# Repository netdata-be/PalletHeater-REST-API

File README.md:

# OpenPelletBridge – REST API for Micronova pellet stoves

> **Nederlandstalige handleiding voor gebruikers: [docs/handleiding.md](docs/handleiding.md).** The technical documentation is listed under [Documentation](#documentation).

> Formerly **PalletHeater**. Renamed after v1.0.0: the default hostname is now `openpelletbridge.local` (a hostname set under *IP settings* is kept), the default MQTT prefix `openpelletbridge` and the release asset `openpelletbridge-firmware.bin` (since v1.1.7 releases no longer carry `palletheater-firmware.bin`: a controller on v1.0.0 needs one manual upload). JSON fields such as `lowPalletAlarm` and the metric `stove_low_pallet_alarm` keep their names for compatibility.

ESP32 firmware that connects to the serial bus of a Micronova based pellet stove and exposes it over:

- a **web app** on `/` to monitor and control the stove from any browser,
- an **HTTP REST API** ([docs/api.md](docs/api.md)),
- a **BLE GATT service** (see [BLE_API.md](BLE_API.md)), used by the iOS app in [app/](app/) (OpenPelletBridge board only: the DevKit firmware is built without Bluetooth, it no longer fits the DevKit's app slot),
- **Prometheus metrics** on `/metrics`,
- a **telnet** debug menu on port 23 (IPv4 and IPv6): status, control, timers, pellets, errors, network, firmware update, live log.

The full OpenAPI 3 specification is in [docs/openapi.json](docs/openapi.json). The same file is embedded in the firmware and rendered with Swagger UI on `http://<device>/api`.

## Documentation

| Document | Contents |
|---|---|
| [docs/handleiding.md](docs/handleiding.md) | Handleiding voor gebruikers (Nederlands) |
| [docs/api.md](docs/api.md) | REST API: conventions, authentication, every endpoint, stove states and error codes |
| [docs/mqtt.md](docs/mqtt.md) | MQTT and Home Assistant, metrics, Bluetooth, telnet |
| [docs/loxone.md](docs/loxone.md) | Loxone: HTTP input with a line of numbers, pushes to the Miniserver (`/jdev/sps/io`), states and error ids |
| [docs/debugging.md](docs/debugging.md) | Serial link, live debugging, restart reason, core dump, firmware updates |
| [docs/development.md](docs/development.md) | Building and uploading, partitions, CI and releases, unit tests, source layout |
| [docs/discovered-values.md](docs/discovered-values.md) | What is known about the stove registers |
| [hardware/README.md](hardware/README.md) | Controller board (draft): schematic, BOM, design choices |
| [docs/openapi.json](docs/openapi.json) | OpenAPI 3 specification |

## Hardware

An ESP32 dev board (`esp32doit-devkit-v1`) on a custom PCB:

N-channel MOSFETs convert the 3.3 V TTL of the ESP32 to the 5 V TTL the stove expects. Micronova uses a single-wire serial bus where TX and RX are coupled, so everything the ESP32 transmits is also received; the firmware strips its own echo from the received bytes. The Fritzing design is in [Fritzing/](Fritzing/).

## Getting started

1. Flash the firmware (see [Development](docs/development.md#development)).
2. On first boot the device starts a WiFi captive portal. Connect to it and enter your WiFi credentials and NTP server.
3. Once connected, the device is reachable on its IP address or on `http://openpelletbridge.local` (mDNS).
4. Open `http://openpelletbridge.local/` for the web app, `http://openpelletbridge.local/device` for the fallback page or `http://openpelletbridge.local/api` for Swagger UI.

Hold the reset button for 5 seconds to wipe the WiFi settings and restart the captive portal.

## Web app

`http://openpelletbridge.local/` (also `/app`) is a single page web app built into the firmware ([web/app.html](web/app.html)). It has no external dependencies, so it also works without internet access, and adapts to phone and desktop screens and to light/dark mode (automatic, or fixed with the theme button).

### A tour of the app

*The screenshots use sample data; names and addresses are examples.*

**Overview.** The top card shows the state of the stove in words (here: standby because energy saving stopped it, and the temperature at which it starts again), the next timer action, the room temperature, set point and fume temperature, and the power button. Below it: set point, flame power and room fan; energy saving with its stop and restart temperatures; and the status values the stove reports. The *Update* button in the header appears when a newer firmware release is available.

**History.** One chart with a lane per quantity on a shared time axis: temperatures, flame power (set and actual), room fan and, on request, fume temperature, auger and fume fan speed. The dotted lines mark every change of the stove state (from the event log), labelled where there is room. Hover or tap for the values at that moment. Choose 30 min up to 24 h (a point every 2 minutes)…

…or *7 d*: hourly averages of the last week, with *Burning*, the share of each hour the stove was heating.

**Remote control, settings and clock.** A read-only copy of what the remote control shows (here *OFF / ENERGY / OK*: standby by energy saving after the stove has cooled down, with the chrono clock icon and the "E" for energy saving), the combustion and pellet quality corrections and the beep, and the stove clock next to NTP and the browser time with buttons to set it.

**Timers.** The six chrono programs of the stove: on and off time, days, set point, flame power and room fan per program, with *Copy to…* to reuse a program. Above them: what the next timer will do.

**Device, network and MQTT** (*Expert* on). Stove and controller firmware, what the firmware is built for, why the controller last (re)started and how often it crashed, Bluetooth and API key, the firmware update from GitHub (*Install vX*), settings backup and restore. *Network (WiFi)* shows the connection and how often it dropped and why; *Other network* and *IP settings* change it. *MQTT* shows the broker connection and opens its settings. *Loxone* sets up the push to a Loxone Miniserver: per value the virtual input that receives it (searched in the Miniserver's own list), the switch that follows on / off, and a test.

**Console** (button *Console* in the header, shown in Debug mode and whenever the stove does not answer; or Ctrl+`). A panel docked at the bottom like the browser's developer tools, with a draggable edge; it stays usable when the stove is unreachable. Three tabs: *Firmware log*, *Stove bus* and *Requests* (the API calls of the page itself with status and duration). *Firmware log* shows what the controller writes to its serial port, with the time; warnings are orange, errors red. After a restart it starts with the last lines from before it. *Log levels per module* sets how much each part writes.

*Stove bus* shows every read and write between the controller and the stove as one line: time, action, register (RAM or EEPROM and address), value (decimal and hex) and what the value means according to the known register table, with the previous value when it changed (*← was 140*). *Changes only* (on by default) shows the first reading of each register and after that only changes, writes and failures. The legend under the output explains the colours. *Raw bytes* adds the bytes of each transaction on the serial line, in hex or (*Binary*) in bits, with what each part is: TX is what the controller sends (read: type, address; write: 0x80 + type, address, value, checksum), RX what it receives: the echo of TX (the bus is one wire), then the stove's answer (checksum, value), with the checksum checked. A timeout shows how many bytes did arrive. Filter on addresses (`0x21, 0x6E`) or text; *Download* saves the lines.

**Dark mode.** The theme button in the header (◐ automatic, ☀ light, ☾ dark) switches between following your phone or computer and a fixed light or dark theme; the choice is kept per browser and included in a settings backup.

### Features

- **Status:** stove state, room / set point / fume temperatures, the sensor the room temperature comes from (derived from the readings), the wireless sensor setting, sensors, fume fan, auger speed, pellet level, error memory, stove vs NTP clock, firmware, starts and working hours. Refreshes every 5 s from `/api/state`.
- **Alerts:** a banner for alarms (states 8 – 10), an active error code, no answer from the stove, low pellets, stale data and an unreachable controller.
- **Settings backup:** *Back up settings* under *Device* downloads a JSON file with the stove settings, timers, MQTT (without password), network, device options and display choices; *Restore settings* writes the parts you tick back through the normal API (no passwords or API key in the file).
- **Status dots:** two dots in the header: *Stove* for the serial link between the controller and the stove (green OK, red the stove does not answer, orange data older than 30 s) and the controller dot for the connection between the page and the controller (green with the time of the last update, red offline). On a phone only the stove dot is shown.
- **Update badge:** when a newer release is available an *Update* button appears in the header, next to the version.
- **Home screen:** the app has a web app manifest and icon (`/manifest.webmanifest`, `/icon.svg`, `/icon-180.png`), so *Add to Home Screen* (iOS Safari, Android Chrome) gives it its own icon and a full-screen window. (Installing as a real PWA, and browser push notifications, need HTTPS with a certificate the device trusts: open `https://openpelletbridge.local/` after installing the controller's self-signed certificate on it, see [`/api/https`](docs/api.md#apihttps); the home screen shortcut works over HTTP too.)
- **History:** one chart for the last 30 min / 1 / 6 / 12 / 24 h or 7 days (hourly averages, with the share of each hour the stove was burning) (from `/api/history`) with toggles for room, set point, stove sensor, remote sensor, flame power, room fan, fume temperature, auger speed, fume fan speed and vertical lines at the exact stove state changes (from `/api/events`), plus a list of the state changes with their duration. Each quantity has its own lane and scale on a shared time axis, with one crosshair tooltip and a table view.
- **Remote control:** a read-only mirror of the remote display (time and date, room temperature, flame power blocks 1 – 4, room fan, "E" for energy saving, OFF screen, error, open menu) plus menu, selected parameter, language and last contact.
- **Controls:** power on/off, set point, flame power, room fan, energy saving, combustion and pellet quality, beep, clock sync, delete single errors or the whole error memory, restart.
- **Timers:** edit, enable/disable and copy PR1 – PR6 (to one program or all others), plus the next scheduled timer action. A program that could not be read from the stove is shown as *Read error* and cannot be saved, so a bad read is never written back.
- **Help:** (i) buttons next to settings, clock, timers and error codes with explanations taken from the stove manual (FWAR01).
- **Clock:** sync the stove clock to NTP or to the browser time.
- **Expert / Debug:** two toggles in the header (remembered per browser). *Expert* shows technical details: wireless sensor setting, fume fan, auger, brazier cleaning countdown, controller firmware / build / uptime, firmware upload, API / metrics links and the history table. *Debug* shows research and diagnostics: raw registers (room fan power RAM 0x0A, pellet reserve sensor / counter, raw remote edit value), serial errors and retries, the telnet switch and the EEPROM presets per power level (auger, fume fan). What is not verified yet is in [docs/discovered-values.md](docs/discovered-values.md).
- **Network and MQTT:** a *Network (WiFi)* card (network, signal, IP address, gateway, hostname; DHCP or static IP and hostname can be changed), an *MQTT* card (connection status, broker, topic prefix, discovery; settings) and a *Loxone* card (Miniserver push, see [Loxone](docs/loxone.md)). A small page with links is on `/device`.
- **Unreachable:** when the controller does not answer every card is greyed out and disabled; when only the stove does not answer (state −1) every card except *Device* is.
- **Language:** Dutch when the remote control language is NLD, otherwise English; `/app?lang=nl` / `/app?lang=en` overrides it.

To change the app, edit `web/app.html` and rebuild; it is embedded gzipped via `board_build.embed_files` like the OpenAPI spec.

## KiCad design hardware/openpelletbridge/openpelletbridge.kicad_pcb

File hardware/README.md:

# Controller board (draft 0.1)

[← README](../README.md)

A small board for the controller: ESP32-S3 module, USB-C, power from the stove or from USB, an isolated interface to the Micronova serial line, status LEDs, a buzzer, two buttons, test pads and four M2 mounting holes. **Draft: schematic and a first routed PCB.** Have it reviewed before ordering.

| File | |
|---|---|
| [openpelletbridge/openpelletbridge.pdf](openpelletbridge/openpelletbridge.pdf) | Schematic (PDF) |
| [openpelletbridge/openpelletbridge.kicad_sch](openpelletbridge/openpelletbridge.kicad_sch) | KiCad 10 schematic (open the `.kicad_pro`) |
| [openpelletbridge/bom.csv](openpelletbridge/bom.csv) | Bill of materials |
| [TODO.md](TODO.md) | **What has to happen when the board is made and taken into use** (checks, firmware port) |
| [openpelletbridge/openpelletbridge.net](openpelletbridge/openpelletbridge.net) | Netlist |
| [openpelletbridge/openpelletbridge.kicad_pcb](openpelletbridge/openpelletbridge.kicad_pcb) | PCB, 40 × 57 mm, 2 layers |
| [tools/gen_schematic.py](tools/gen_schematic.py) | Generates the schematic: the netlist is defined there |
| [tools/gen_pcb.py](tools/gen_pcb.py) | Generates the PCB: placement, outline, rules, isolation, planes |
| [tools/build.sh](tools/build.sh) | Schematic → ERC → netlist → PCB → [Freerouting](https://github.com/freerouting/freerouting) → planes → DRC |

The schematic is generated: change [tools/gen_schematic.py](tools/gen_schematic.py), then

```bash
python3 hardware/tools/gen_schematic.py
cd hardware/openpelletbridge
kicad-cli sch erc --severity-all openpelletbridge.kicad_sch        # 0 violations
kicad-cli sch export pdf openpelletbridge.kicad_sch
```

The whole chain, PCB included (KiCad 10 and Java; Freerouting is the open-source autorouter):

```bash
FREEROUTING=/path/to/freerouting-2.5.0.jar hardware/tools/build.sh
```

Freerouting is chaotic: a small change can leave a few connections open, so the script tries three strategies (all nets at once, signals first, ground planes first) until DRC finds no unconnected item. Once the board is finished by hand in KiCad, the KiCad files become the source and the scripts are no longer used.

## PCB

40 × 57 mm, 2 layers, all parts on the top (THT: J1 shell, J2); the bottom has only test pads and text, so nothing is assembled there. Antenna at the top edge (no copper below it on either layer), USB-C and the stove connector side by side on the bottom edge. Ground planes on both layers with stitching vias: GND for the controller, GND_S on the stove side (bottom left). A copper-free strip separates the two sides under the optocouplers; only JP1 / JP2 cross it. Four M2 holes (not plated, no copper within 2.4 mm, so a metal screw or standoff connects nothing): two at the sides of the buzzer band, two in the bottom corners. The top corners are in the antenna keep-out of the module (Espressif: no metal within 15 mm of the antenna).

Rules: tracks 0.2 mm (power 0.4 mm), clearance 0.2 mm, vias 0.6 / 0.3 mm, 0.3 mm from the board edge: within the standard capabilities of the usual PCB makers. DRC: no errors, no unconnected items; the remaining warnings are silkscreen (module outline over the top edge, labels close to parts).

Silkscreen: descriptions instead of references (USB-C, OPTO TX / OPTO RX, BUZZER, 5V BUCK, 3V3 LDO; the references are in the assembly drawing), GND / 5V / 20V / DATA at the stove connector, RESET and BOOT at the buttons, SYS · STOVE under the status LEDs, TX and RX at the serial LEDs (each just above its optocoupler, so they read as part of the stove link), STOVE PWR with + (JP1, 20 V) and − (JP2, ground) at the solder jumpers. On the bottom: the names of the test pads, "Micronova serial port board" (in the copper-free antenna strip), the name and version, and the input range "Power: 12-24 V DC (stove) or USB-C 5 V".

Not yet done: a final manual review of the routing (the autorouter's tracks are functional, not pretty). Production files: see *Ordering* below; open checks: [TODO.md](TODO.md).

3D models the KiCad library lacks are in [openpelletbridge/3d](openpelletbridge/3d): the ESP32-S3-MINI-1 from Espressif's [kicad-libraries](https://github.com/espressif/kicad-libraries), the WS2812B-2020 (C965555), the TS-1187A buttons (C318884) and the Kefa header (C441173, footprint in [openpelletbridge/openpelletbridge.pretty](openpelletbridge/openpelletbridge.pretty)) from LCSC / EasyEDA (fetched with easyeda2kicad).

## Case

3D printable case, [case/openpelletbridge-case.scad](case/openpelletbridge-case.scad) ([OpenSCAD](https://openscad.org), parametric), ready to print: [base](case/openpelletbridge-case-base.stl) and [lid](case/openpelletbridge-case-lid.stl). Outside 45 × 62 × 16.4 mm (plus two mounting ears with a 4.2 mm hole; `ears = false` without).

- **No screws:** the board (1.6 mm) drops onto four standoffs whose 1.9 mm pegs go into its M2 holes, and the lid's four clamping tubes press it onto the standoffs. The lid clicks in with four snap hooks (two per long side) that catch in windows in the walls; to open, push the hooks in through the windows with a small screwdriver. (The board's holes are M2, 2.2 mm, not plated, no copper within 2.4 mm, if you ever want screws instead.)
- **Buttons:** BOOT and RESET are flexure tongues in the lid with a plunger 0.3 mm above the tactile switch.
- **LEDs:** solid light pipes (2.2 mm) from the translucent lid down to just above SYS, STOVE, TX and RX; a slot in the lid's underside between SYS and STOVE keeps their colours apart. `solid_pipes = false` gives hollow tubes with a hole through the lid instead (for an opaque lid).
- **Connectors:** opening for the USB-C cable's overmould (13 × 7.5 mm); the stove connector's notch is open through the lid, so a cable plug of any height fits.
- **Other:** sound holes above the buzzer, engraved button labels (BOOT, RST; no other text: small engraved text gives thin-wall errors in resin). Plastic only near the antenna (top edge).
- **Material:** ordered in resin at JLCPCB (JLC3DP): base in **9600 Resin White** (sanding), lid in **8001 Resin Translucent** (fine sanding). Resin is brittle: the hook arms are 0.9 mm with a fillet at the root (~1.3 % strain when they click in), and no wall is under JLC3DP's 0.8 mm minimum. Ask for the supports on the inside of the lid, so the top stays smooth. Open the lid gently, and use a washer on the mounting ears.
- **FDM instead:** base upright, lid upside down (top face on the bed), 0.2 mm layers, no supports; PETG rather than PLA for the hooks.
- **Checked** against the board's 3D model (KiCad STL export): no part of the case inside a component, and the lid's hooks sit in the windows, not in the walls. Regenerate after a board change: `kicad-cli pcb export stl --subst-models --user-origin 100x157mm -o case/board.stl openpelletbridge/openpelletbridge.kicad_pcb`, then `openscad -D 'part="base"' -o … case/openpelletbridge-case.scad` (`"lid"`, or `"assembly"` with the board).

## Design

| Block | Choice | Why |
|---|---|---|
| Module | ESP32-S3-MINI-1-N8 (15.4 × 20.5 mm) | 8 MB flash (the firmware uses 91 % of a 4 MB layout), dual core, BLE 5, native USB: no USB-serial chip or auto-reset circuit |
| USB | USB-C GCT USB4105-GF-A, 5.1 kΩ on CC1 / CC2, USBLC6-2SC6, 0.5 A PTC | Power and flashing / console from a PC; D+ / D- straight to IO20 / IO19 |
| Stove power | 20 V → AP63205 step-down → 5 V, 0.35 A / 30 V PTC, 24 V TVS | A 7805 from 20 V burns ~3 W at the WiFi peaks. Input range **12 – 24 V**: above 24 V the TVS starts to conduct; worst case (WiFi peak, buzzer, LEDs full white) the board takes ~2.9 W, 0.24 A at 12 V, below the 350 mA hold current of F2. The buck itself needs ~7 V for 5 V out. F2 mainly protects the stove: a short on this board, or the TVS clamping, trips it instead of loading the stove's supply |
| Stove 5 V | Only for the LED of the RX optocoupler U6 (a few mA) | The controller never runs from the stove's 5 V |
| Power mux | TPS2116 in priority mode: stove (VIN1) first, USB (VIN2) as fallback; then AP2112K-3.3 | Both sources at once: with the stove's 5 V present the board runs from the stove and USB only carries data. USB takes over when the stove's 5 V drops below ~4.3 V (33k / 10k on PR1; VREF 1.0 V ± 8 % gives 4.0 – 4.6 V). Break-before-make in ~8 µs (22 µF on +5V: ~0.2 V dip at 0.5 A), reverse current blocked both ways. ST → IO4: high = powered by the stove. Replaces two LM66100 ideal diodes, which had CE on GND and so did not block reverse current (TI: only with CE on VOUT) and had no priority between two ~5 V sources |
| Isolation | JP1 + JP2 (solder jumpers) | Open: USB powered, stove side galvanically isolated. Closed: powered by the stove; GND_S is then tied to GND (and to the PC on USB) |
| Serial line | 2× LTV-357T (SO-4) | Level shift 3.3 V ↔ 5 V and isolation; the stove side runs on the stove's 5 V |
| Echo | Kept | The firmware tells "bus not connected" (no echo) from "stove does not answer" (echo, no answer) |
| TX / RX LED | Two 0603 LEDs on the serial lines themselves (no GPIO), above the optocouplers | Red = TX, green = RX: both while sending (echo), green when the stove answers, red only = no bus. They stay on the ESP side of the isolation (3V3, STOVE_TX / STOVE_RX) |
| Reverse polarity | B5819W Schottky in series with the stove's 20 V (after F2) | The stove's pin order is not standard: a swapped cable gives no current instead of a dead step-down. ~0.3 V drop at 0.1 A, no matter for the step-down |
| Buzzer | MLT-5020 magnetic transducer 5 × 5 mm on 3.3 V, AO3400A on IO21, 1N4148W flyback diode, 10 kΩ pull-down, 10 µF buffer | Needs a PWM signal (~4 kHz, LEDC); ~110 mA while it sounds. Silent during boot (pull-down). Operating temperature −30 – 70 °C: mind the place inside the stove |
| Test pads | 9 pads (1.5 mm) on the bottom: 3V3, 5V, GND, TX, RX under the module; 20V, 5V_S, DATA, GND_S on the stove side | Measuring at bring-up without probing the parts |
| Status LEDs | 2× WS2812B-2020 on IO8 via SN74LV1T34 (R8 10 kΩ pull-down on its input) | LED1 system (WiFi / Bluetooth / telnet / power), LED2 stove state; any colour and blink pattern, one GPIO |
| Buttons | RESET (EN, 10 kΩ / 1 µF) and BOOT / USER (IO0) | IO0 held during reset = download mode; otherwise a user button: 1× click / mute an alarm, 2× LEDs on / off, 3× buzzer on / off, hold 3 s = full reset countdown (8 s = reset, release = abort), see src/boardButton.h |
| Stove connector | Cixi Kefa KF2EDGR-3.5-4P header (LCSC C441173, 3.5 mm, right angle, THT); cable plug **KF2EDGKD-3.5-4P** (LCSC C441073, spring terminals, wires up to 1.5 mm²) | Same series from one maker, both at LCSC, so the plug surely fits; push the wires in, no crimping. Footprint and 3D model from LCSC / EasyEDA (holes 1.4 mm: the Phoenix footprint has 1.2 mm) |

### Serial interface

```
TX:  +3V3 ─ R5 220 ─ LED(U5) ─ STOVE_TX (IO17)          U5 transistor: DATA_S ─ GND_S
RX:  +5V_S ─ LED(U6) ─ R6 1.5k ─ DATA_S                  U6 transistor: STOVE_RX (IO18, 10k pull-up) ─ GND
```

STOVE_TX low switches U5 on and pulls the stove's data line low. Whenever DATA is low (the stove or our own TX), U6 pulls STOVE_RX low. R12 keeps STOVE_TX high while the ESP boots, so nothing reaches the bus before the UART runs. At 1200 baud (833 µs per bit) the optocouplers are fast enough.

Currents (Vf: optocoupler LED ~1.2 V, D5 / D6 ~2 V):

| Path | Current |
|---|---|
| IO17 low: U5 LED (R5 220) + D5 (R10 1.5k) + R12 | 9.5 + 0.9 + 0.3 = **10.7 mA** sunk by IO17 |
| DATA low: U6 LED from the stove's 5 V (R6 1.5k) | **2.5 mA**: the extra load on the stove's bus |
| U5 transistor, our TX | must sink the stove's pull-up + 2.5 mA; at CTR ≥ 100 % it can sink ≥ 9.5 mA, so the stove's pull-up may be down to ~750 Ω |
| U6 transistor, RX | R7 0.33 mA + D6 0.8 mA = 1.1 mA of the ≥ 2.5 mA it can sink |

D5 / D6 cannot change the logic levels: each sits between 3V3 (through 1.5k) and a line that is either high (3.3 V: no current) or pulled low by IO17 / U6, which then sink 0.8 – 0.9 mA more. While the ESP boots, STOVE_TX is high-impedance and R12 holds it high: D5 and U5 stay off, nothing reaches the bus. The stove's DATA pull-up is not known: measure it before connecting (see [TODO.md](TODO.md)).

### GPIO

| GPIO | Use |
|---|---|
| IO17 | STOVE_TX (UART1 TX) |
| IO18 | STOVE_RX (UART1 RX) |
| IO8 | WS2812B data |
| IO0 | BOOT / user button |
| IO21 | Buzzer (PWM, via Q1) |
| IO4 | Power source (TPS2116 ST): high = stove, low = USB |
| IO19 / IO20 | USB D- / D+ |
| EN | RESET button |

The strapping pins IO3, IO45 and IO46 are left unconnected (their defaults are right). Free for later: IO1, IO2, IO5 – IO7, IO9 – IO16, IO33 – IO42, IO47, IO48 (IO35 – IO37 only because the N8 has no PSRAM); TXD0 / RXD0 (IO43 / IO44) are the ROM boot log.

## Ordering: two assemblers

Every part has an **LCSC** number (JLCPCB) and a **Manufacturer + MPN** (Aisler and anyone buying at Mouser / DigiKey / Farnell). Where the LCSC part is a Chinese-market equivalent, the MPN is a part with the same footprint and pinout:

| Ref | LCSC (JLCPCB) | MPN (Aisler, Mouser, DigiKey) |
|---|---|---|
| R* | UNI-ROYAL 0603WAF… | YAGEO RC0603FR-07… |
| D5 / D6 | KENTO KT-0603R / KT-0603YG | Kingbright APT1608SURCK / APT1608CGCK |
| U8 | TI TPS2116DRLR (C3235557) | TI TPS2116DRLR |
| J1 | GCT USB4105-GF-A (C3020560): **not in JLCPCB's own stock; pre-order it from LCSC into your JLCPCB parts library** (Parts Manager → pre-order / global sourcing) | GCT USB4105-GF-A |
| J2 | Cixi Kefa KF2EDGR-3.5-4P (plug KF2EDGKD-3.5-4P, C441073) | Phoenix Contact 1844236 (plug FMC 1,5/4-ST-3,5, 1952283) |
| LED1 / LED2 | Xinglight XL-2020RGBC-WS2812B | Worldsemi WS2812B-2020 |
| SW1 / SW2 | XKB TS-1187A-B-A-B | C&K PTS526 SM15 SMTR2 LFS |
| D8 | JSCJ B5819W SL | onsemi MBR0540T1G |
| BZ1 | Huaneng MLT-5020 | Same Sky CMT-5023S-SMT-TR (same 5 × 5 mm size; **pads not checked** against this footprint) |

Files in `openpelletbridge/production/`: JLCPCB `bom-jlcpcb.csv` + `cpl-jlcpcb.csv` (with the rotation / offset corrections for JLCPCB's part models); Aisler and others `bom-mpn.csv` + `positions.csv`, or the KiCad project itself (the footprints carry the Manufacturer / MPN fields).

## Open points

Kept in [TODO.md](TODO.md): checks before ordering, bring-up, firmware port.

## Firmware

The board needs an ESP32-S3 build of the firmware: see [TODO.md](TODO.md).

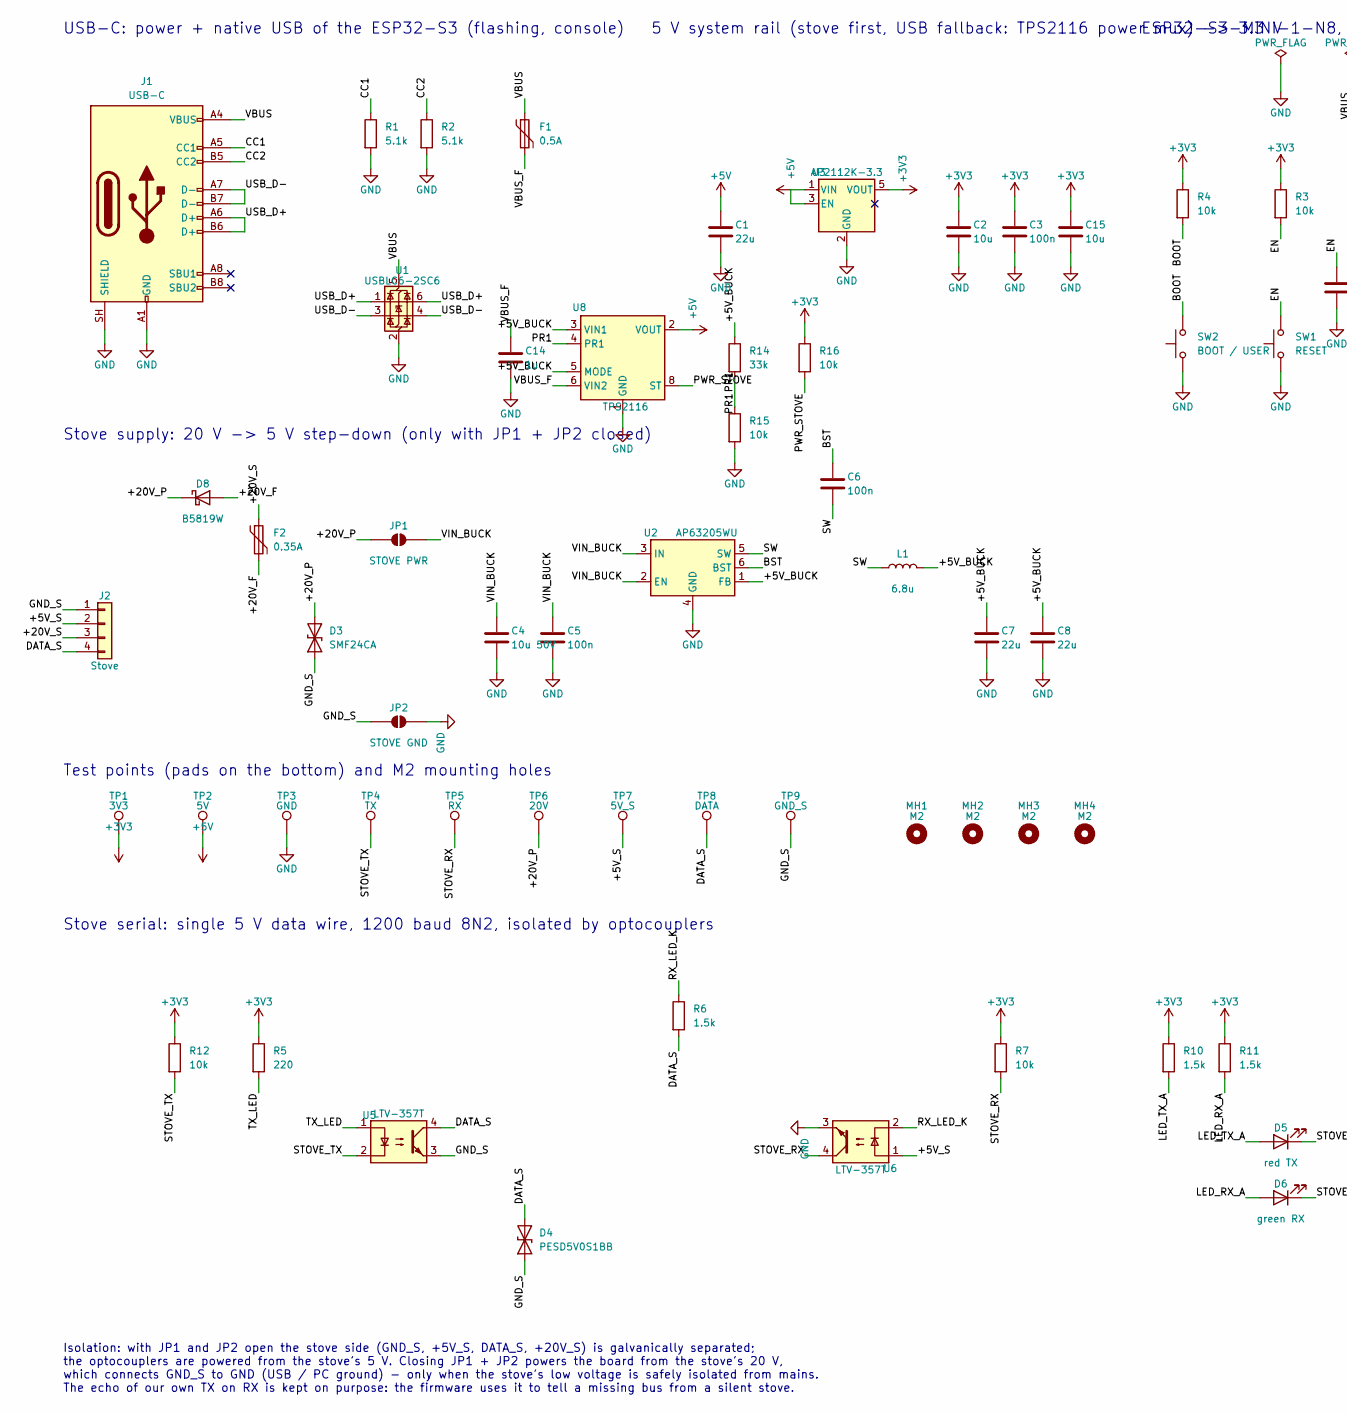
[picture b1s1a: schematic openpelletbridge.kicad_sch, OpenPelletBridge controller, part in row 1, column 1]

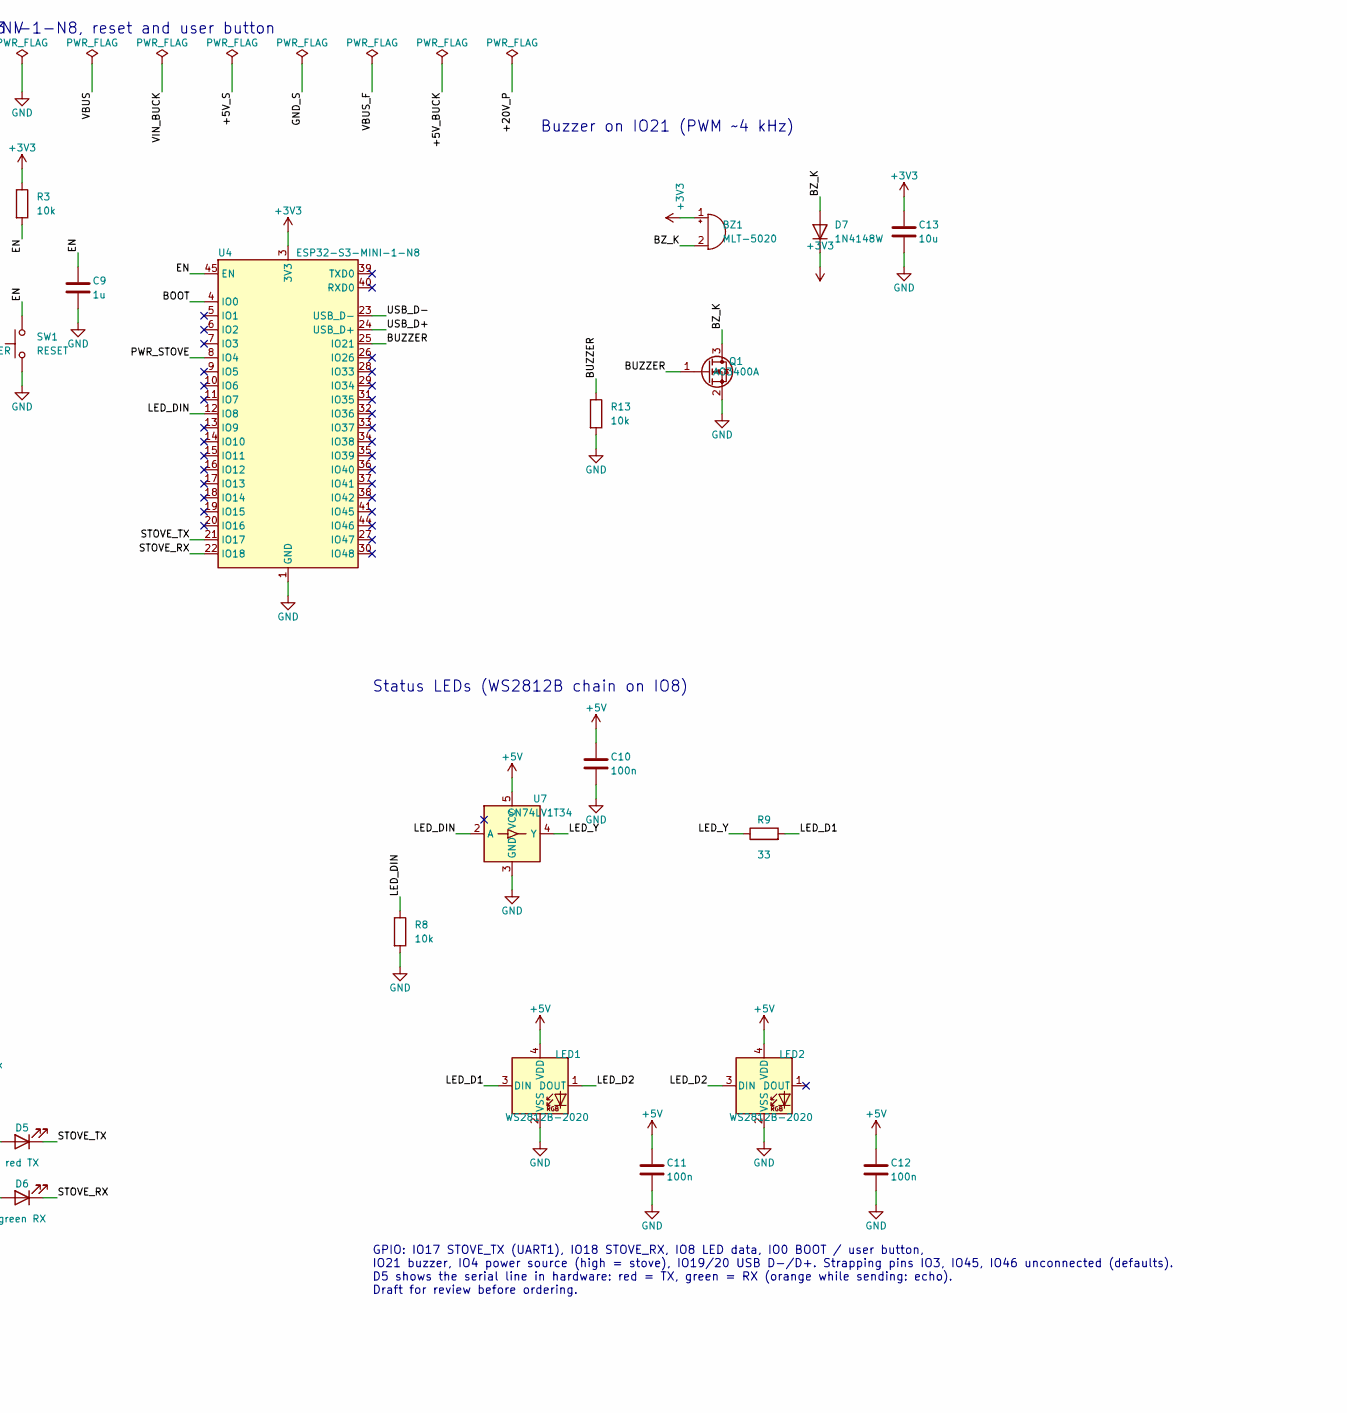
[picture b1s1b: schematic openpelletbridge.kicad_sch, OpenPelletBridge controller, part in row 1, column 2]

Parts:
BZ1: MLT-5020; Buzzer_Huaneng_MLT-5020; MPN CMT-5023S-SMT-TR; LCSC C94598
C1, C7, C8: 22u; C_0805_2012Metric; MPN CL21A226MAQNNNE; LCSC C45783
C2, C13, C15: 10u; C_0805_2012Metric; MPN CL21A106KAYNNNE; LCSC C15850
C3, C5, C6, C10, C11, C12: 100n; C_0603_1608Metric; MPN CC0603KRX7R9BB104; LCSC C14663
C4: 10u 50V; C_1206_3216Metric; MPN CL31A106KBHNNNE; LCSC C13585
C9, C14: 1u; C_0603_1608Metric; MPN CL10A105KB8NNNC; LCSC C15849
D3: SMF24CA; D_SOD-123F; MPN SMF24CA; LCSC C19077515
D4: PESD5V0S1BB; D_SOD-323; MPN PESD5V0S1BB,115; LCSC C2687128
D5: red TX; LED_0603_1608Metric; MPN APT1608SURCK; LCSC C2286
D6: green RX; LED_0603_1608Metric; MPN APT1608CGCK; LCSC C2289
D7: 1N4148W; D_SOD-123; MPN 1N4148W-7-F; LCSC C81598
D8: B5819W; D_SOD-123; MPN MBR0540T1G; LCSC C8598
F1: 0.5A; Fuse_1206_3216Metric; MPN 1206L050/15YR; LCSC C315893
F2: 0.35A; Fuse_1206_3216Metric; MPN 1206L035/30WR; LCSC C2153989
J1: USB-C; USB_C_Receptacle_GCT_USB4105-xx-A_16P_TopMnt_Horizontal; MPN USB4105-GF-A; LCSC C3020560
J2: Stove; KF2EDGR-3.5-4P; MPN 1844236; LCSC C441173
JP1: STOVE PWR; SolderJumper-2_P1.3mm_Open_RoundedPad1.0x1.5mm
JP2: STOVE GND; SolderJumper-2_P1.3mm_Open_RoundedPad1.0x1.5mm
L1: 6.8u; L_Bourns-SRN4018; MPN SRN4018-6R8M; LCSC C2044369
LED1, LED2: WS2812B-2020; LED_WS2812B-2020_PLCC4_2.0x2.0mm; MPN WS2812B-2020; LCSC C5349955
MH1, MH2, MH3, MH4: M2; MountingHole_2.2mm_M2
Q1: AO3400A; SOT-23; MPN AO3400A; LCSC C20917
R1, R2: 5.1k; R_0603_1608Metric; MPN RC0603FR-075K1L; LCSC C23186
R3, R4, R7, R8, R12, R13, R15, R16: 10k; R_0603_1608Metric; MPN RC0603FR-0710KL; LCSC C25804
R5: 220; R_0603_1608Metric; MPN RC0603FR-07220RL; LCSC C22962
R6, R10, R11: 1.5k; R_0603_1608Metric; MPN RC0603FR-071K5L; LCSC C22843
R9: 33; R_0603_1608Metric; MPN RC0603FR-0733RL; LCSC C23140
R14: 33k; R_0603_1608Metric; MPN RC0603FR-0733KL; LCSC C4216
SW1: RESET; SW_Push_1P1T_XKB_TS-1187A; MPN PTS526 SM15 SMTR2 LFS; LCSC C318884
SW2: BOOT / USER; SW_Push_1P1T_XKB_TS-1187A; MPN PTS526 SM15 SMTR2 LFS; LCSC C318884
TP1: 3V3; TestPoint_Pad_D1.5mm
TP2: 5V; TestPoint_Pad_D1.5mm
TP3: GND; TestPoint_Pad_D1.5mm
TP4: TX; TestPoint_Pad_D1.5mm
TP5: RX; TestPoint_Pad_D1.5mm
TP6: 20V; TestPoint_Pad_D1.5mm
TP7: 5V_S; TestPoint_Pad_D1.5mm
TP8: DATA; TestPoint_Pad_D1.5mm
TP9: GND_S; TestPoint_Pad_D1.5mm
U1: USBLC6-2SC6; SOT-23-6; MPN USBLC6-2SC6; LCSC C2827654
U2: AP63205WU; TSOT-23-6; MPN AP63205WU-7; LCSC C2071056
U3: AP2112K-3.3; SOT-23-5; MPN AP2112K-3.3TRG1; LCSC C23380830
U4: ESP32-S3-MINI-1-N8; ESP32-S2-MINI-1; MPN ESP32-S3-MINI-1-N8; LCSC C2913206
U5, U6: LTV-357T; SO-4_4.4x3.6mm_P2.54mm; MPN LTV-357T; LCSC C119089
U7: SN74LV1T34; SOT-23-5; MPN SN74LV1T34DBVR; LCSC C100024
U8: TPS2116; SOT-583-8; MPN TPS2116DRLR; LCSC C3235557

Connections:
+3V3: BZ1.1 (+), C2.1, C3.1, C13.1, C15.1, D7.1 (K), R3.1, R4.1, R5.1, R7.1, R10.1, R11.1, R12.1, R16.1, TP1.1, U3.5 (VOUT), U4.3 (3V3)
+5V: C1.1, C10.1, C11.1, C12.1, LED1.4 (VDD), LED2.4 (VDD), TP2.1, U3.1 (VIN), U3.3 (EN), U7.5 (VCC), U8.2 (VOUT), U8.7 (VOUT)
/+5V_BUCK: C7.1, C8.1, L1.2, R14.1, U2.1 (FB), U8.3 (VIN1), U8.5 (MODE)
/+5V_S: J2.2, TP7.1, U6.1
/+20V_F: D8.2 (A), F2.2
/+20V_P: D3.2 (A2), D8.1 (K), JP1.1 (A), TP6.1
/+20V_S: F2.1, J2.3
/BOOT: R4.2, SW2.2, U4.4 (IO0)
/BST: C6.1, U2.6 (BST)
/BUZZER: Q1.1 (G), R13.1, U4.25 (IO21)
/BZ_K: BZ1.2 (-), D7.2 (A), Q1.3 (D)
/CC1: J1.A5 (CC1), R1.1
/CC2: J1.B5 (CC2), R2.1
/DATA_S: D4.2 (A2), J2.4, R6.2, TP8.1, U5.4
/EN: C9.1, R3.2, SW1.2, U4.45 (EN)
/GND_S: D3.1 (A1), D4.1 (A1), J2.1, JP2.1 (A), TP9.1, U5.3
/LED_D1: LED1.3 (DIN), R9.2
/LED_D2: LED1.1 (DOUT), LED2.3 (DIN)
/LED_DIN: R8.1, U4.12 (IO8), U7.2 (A)
/LED_RX_A: D6.2 (A), R11.2
/LED_TX_A: D5.2 (A), R10.2
/LED_Y: R9.1, U7.4 (Y)
/PR1: R14.2, R15.1, U8.4 (PR1)
/PWR_STOVE: R16.2, U4.8 (IO4), U8.8 (ST)
/RX_LED_K: R6.1, U6.2
/STOVE_RX: D6.1 (K), R7.2, TP5.1, U4.22 (IO18), U6.4
/STOVE_TX: D5.1 (K), R12.2, TP4.1, U4.21 (IO17), U5.2
/SW: C6.2, L1.1, U2.5 (SW)
/TX_LED: R5.2, U5.1
/USB_D+: J1.A6 (D+), J1.B6 (D+), U1.1 (I/O1), U1.6 (I/O1), U4.24 (USB_D+)
/USB_D-: J1.A7 (D-), J1.B7 (D-), U1.3 (I/O2), U1.4 (I/O2), U4.23 (USB_D-)
/VBUS: F1.1, J1.A4 (VBUS), J1.A9 (VBUS), J1.B4 (VBUS), J1.B9 (VBUS), U1.5 (VBUS)
/VBUS_F: C14.1, F1.2, U8.6 (VIN2)
/VIN_BUCK: C4.1, C5.1, JP1.2 (B), U2.2 (EN), U2.3 (IN)
GND: C1.2, C2.2, C3.2, C4.2, C5.2, C7.2, C8.2, C9.2, C10.2, C11.2, C12.2, C13.2, C14.2, C15.2, J1.A1 (GND), J1.A12 (GND), J1.B1 (GND), J1.B12 (GND), J1.SH (SHIELD), JP2.2 (B), LED1.2 (VSS), LED2.2 (VSS), Q1.2 (S), R1.2, R2.2, R8.2, R13.2, R15.2, SW1.1, SW2.1, TP3.1, U1.2 (GND), U2.4 (GND), U3.2 (GND), U4.1 (GND), U4.2 (GND), U4.42 (GND), U4.43 (GND), U4.46 (GND), U4.47 (GND), U4.48 (GND), U4.49 (GND), U4.50 (GND), U4.51 (GND), U4.52 (GND), U4.53 (GND), U4.54 (GND), U4.55 (GND), U4.56 (GND), U4.57 (GND), U4.58 (GND), U4.59 (GND), U4.60 (GND), U4.61 (GND), U4.62 (GND), U4.63 (GND), U4.64 (GND), U4.65 (GND), U6.3, U7.3 (GND), U8.1 (GND)

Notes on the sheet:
USB-C: power + native USB of the ESP32-S3 (flashing, console)
5 V system rail (stove first, USB fallback: TPS2116 power mux) -> 3.3 V
Stove supply: 20 V -> 5 V step-down (only with JP1 + JP2 closed)
ESP32-S3-MINI-1-N8, reset and user button
Stove serial: single 5 V data wire, 1200 baud 8N2, isolated by optocouplers
Status LEDs (WS2812B chain on IO8)
Buzzer on IO21 (PWM ~4 kHz)
Test points (pads on the bottom) and M2 mounting holes
Isolation: with JP1 and JP2 open the stove side (GND_S, +5V_S, DATA_S, +20V_S) is galvanically separated; the optocouplers are powered from the stove's 5 V. Closing JP1 + JP2 powers the board from the stove's 20 V, which connects GND_S to GND (USB / PC ground) - only when the stove's low voltage is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
GPIO: IO17 STOVE_TX (UART1), IO18 STOVE_RX, IO8 LED data, IO0 BOOT / user button, IO21 buzzer, IO4 power source (high = stove), IO19/20 USB D-/D+. Strapping pins IO3, IO45, IO46 unconnected (defaults). D5 shows the serial line in hardware: red = TX, green = RX (orange while sending: echo). Draft fo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

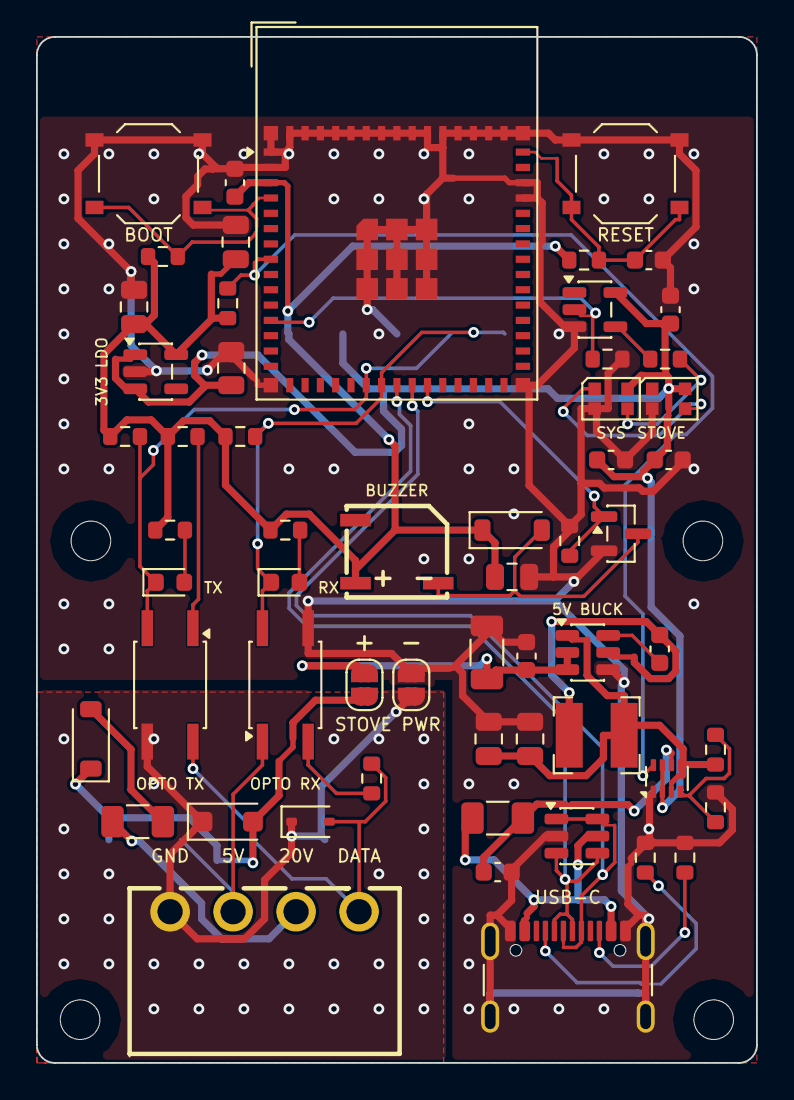
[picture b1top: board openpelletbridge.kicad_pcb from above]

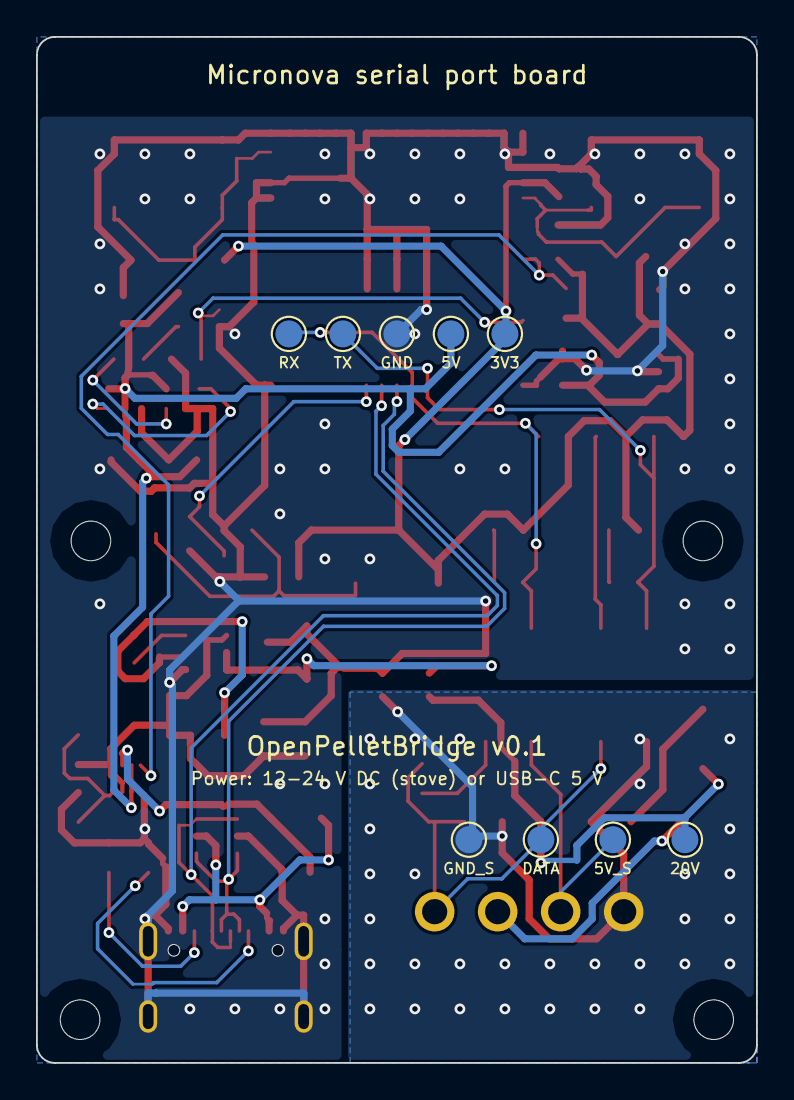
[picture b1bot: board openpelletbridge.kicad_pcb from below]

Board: 2 copper layers, 40.0 x 57.0 mm, 71 parts (9 on the bottom side), 35 nets.

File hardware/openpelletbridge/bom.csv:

"Refs","Value","Footprint","MPN","Note","Qty"
"BZ1","MLT-5020","openpelletbridge:Buzzer_Huaneng_MLT-5020","CMT-5023S-SMT-TR","Magnetic transducer, needs a PWM signal (4 kHz); pad 3 is mechanical","1"
"C1,C7,C8","22u","Capacitor_SMD:C_0805_2012Metric","CL21A226MAQNNNE","","3"
"C2,C13,C15","10u","Capacitor_SMD:C_0805_2012Metric","CL21A106KAYNNNE","Buffer for the buzzer current pulses,Bulk at module pin 3 (WiFi peaks); C2 stays at the LDO","3"
"C3,C5,C6,C10-C12","100n","Capacitor_SMD:C_0603_1608Metric","CC0603KRX7R9BB104","Bootstrap,Next to module pin 3","6"
"C4","10u 50V","Capacitor_SMD:C_1206_3216Metric","CL31A106KBHNNNE","","1"
"C9,C14","1u","Capacitor_SMD:C_0603_1608Metric","CL10A105KB8NNNC","EN delay (Espressif: 10k / 1uF),Input of the mux, USB side","2"
"D3","SMF24CA","Diode_SMD:D_SOD-123F","SMF24CA","TVS 24 V on the stove supply","1"
"D4","PESD5V0S1BB","Diode_SMD:D_SOD-323","PESD5V0S1BB,115","ESD on the stove data line","1"
"D5","red TX","LED_SMD:LED_0603_1608Metric","APT1608SURCK","~0.8 mA","1"
"D6","green RX","LED_SMD:LED_0603_1608Metric","APT1608CGCK","yellow-green, Vf 2.0-2.2 V (an InGaN green needs ~3 V)","1"
"D7","1N4148W","Diode_SMD:D_SOD-123","1N4148W-7-F","Flyback diode across the buzzer coil","1"
"D8","B5819W","Diode_SMD:D_SOD-123","MBR0540T1G","Reverse polarity protection: a swapped stove cable gives no current (~0.3 V drop at 0.1 A)","1"
"F1","0.5A","Fuse:Fuse_1206_3216Metric","1206L050/15YR","PTC, hold 500 mA","1"
"F2","0.35A","Fuse:Fuse_1206_3216Metric","1206L035/30WR","PTC, hold 350 mA, 30 V: worst case ~2.9 W in = 0.24 A at 12 V","1"
"J1","USB-C","Connector_USB:USB_C_Receptacle_GCT_USB4105-xx-A_16P_TopMnt_Horizontal","USB4105-GF-A","","1"
"J2","Stove","openpelletbridge:KF2EDGR-3.5-4P","1844236","Pin order of the stove varies: measure GND / 5 V / 20 V / DATA first. Cable plug: Kefa KF2EDGKD-3.5-4P (LCSC C441073, spring) with the Kefa header, Phoenix FMC 1,5/4-ST-3,5 (1952283, push-in) with the Phoenix header","1"
"L1","6.8u","Inductor_SMD:L_Bourns-SRN4018","SRN4018-6R8M","check the AP63205 datasheet table","1"
"LED1,LED2","WS2812B-2020","LED_SMD:LED_WS2812B-2020_PLCC4_2.0x2.0mm","WS2812B-2020","Stove state,System: WiFi / Bluetooth / telnet / power","2"
"Q1","AO3400A","Package_TO_SOT_SMD:SOT-23","AO3400A","Logic-level N-MOSFET (Vgs(th) ~1.4 V)","1"
"R1,R2","5.1k","Resistor_SMD:R_0603_1608Metric","RC0603FR-075K1L","USB-C sink: 5 V","2"
"R3,R4,R7,R8,R12,R13,R15,R16","10k","Resistor_SMD:R_0603_1608Metric","RC0603FR-0710KL","Buzzer silent while the ESP boots,Keeps TX idle (high) while the ESP boots: no garbage on the stove bus,LEDs stay dark during boot,ST pull-up: high = powered by the stove,U6 sinks 0.33 mA + D6 0.8 mA = 1.1 mA of its 2.5 mA (CTR >= 100 %)","8"
"R5","220","Resistor_SMD:R_0603_1608Metric","RC0603FR-07220RL","U5 LED ~9.5 mA: at CTR >= 100 % U5 sinks the stove's pull-up plus U6's LED current (2.5 mA). IO17 sinks ~10.7 mA in all","1"
"R6,R10,R11","1.5k","Resistor_SMD:R_0603_1608Metric","RC0603FR-071K5L","U6 LED ~2.5 mA when DATA low (load on the stove's bus)","3"
"R9","33","Resistor_SMD:R_0603_1608Metric","RC0603FR-0733RL","","1"
"R14","33k","Resistor_SMD:R_0603_1608Metric","RC0603FR-0733KL","PR1 divider: switch to USB below ~4.3 V","1"
"SW1","RESET","Button_Switch_SMD:SW_Push_1P1T_XKB_TS-1187A","PTS526 SM15 SMTR2 LFS","","1"
"SW2","BOOT / USER","Button_Switch_SMD:SW_Push_1P1T_XKB_TS-1187A","PTS526 SM15 SMTR2 LFS","IO0: user button; held during reset = download mode","1"
"U1","USBLC6-2SC6","Package_TO_SOT_SMD:SOT-23-6","USBLC6-2SC6","ESD protection USB","1"
"U2","AP63205WU","Package_TO_SOT_SMD:TSOT-23-6","AP63205WU-7","Step-down 3.8-32 V -> 5 V, 2 A","1"
"U3","AP2112K-3.3","Package_TO_SOT_SMD:SOT-23-5","AP2112K-3.3TRG1","LDO 600 mA","1"
"U4","ESP32-S3-MINI-1-N8","RF_Module:ESP32-S2-MINI-1","ESP32-S3-MINI-1-N8","8 MB flash, no PSRAM. Footprint of the pin-compatible S2-MINI-1; keep the antenna area free","1"
"U5,U6","LTV-357T","Package_SO:SO-4_4.4x3.6mm_P2.54mm","LTV-357T","RX: DATA low -> STOVE_RX low (also our own TX: echo = self-test),TX: STOVE_TX low -> DATA low. CTR >= 100 %","2"
"U7","SN74LV1T34","Package_TO_SOT_SMD:SOT-23-5","SN74LV1T34DBVR","3.3 V -> 5 V for the LED data; works down to VCC 1.8 V (the 5 V rail can be ~4.6 V on USB)","1"
"U8","TPS2116","Package_TO_SOT_SMD:SOT-583-8","TPS2116DRLR","Power mux, priority mode: stove first, USB as fallback","1"
